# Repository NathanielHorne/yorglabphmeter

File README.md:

# yorglabphmeter
yorglabphmeter

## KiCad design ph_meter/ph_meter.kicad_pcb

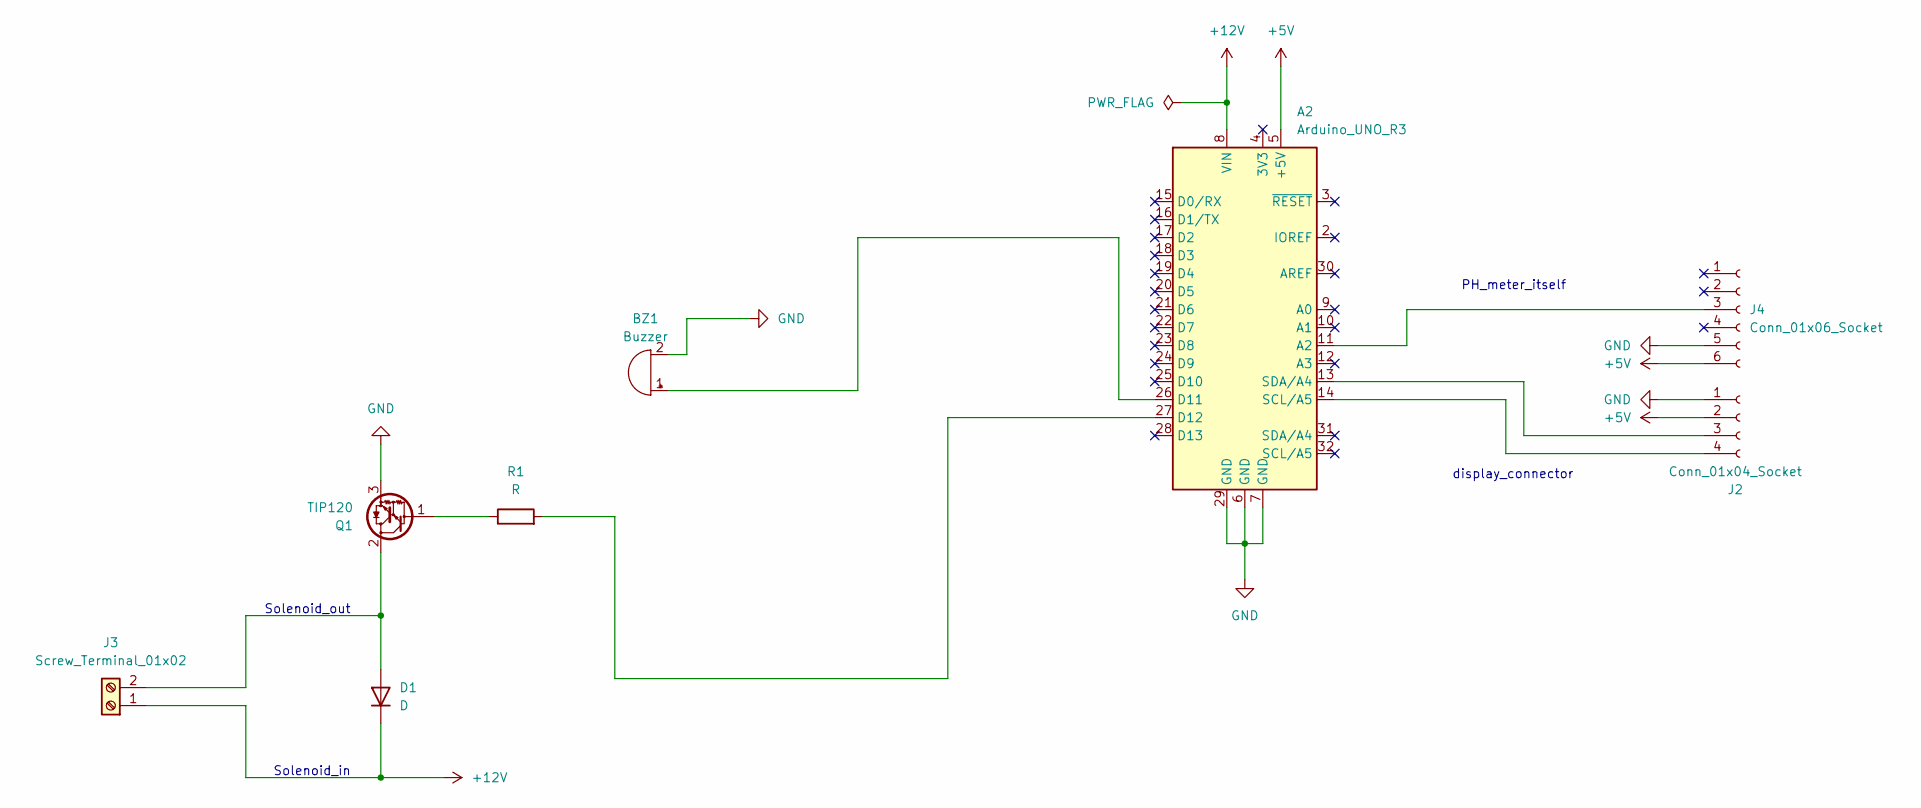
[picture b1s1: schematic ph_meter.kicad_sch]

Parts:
A2: Arduino_UNO_R3
BZ1: Buzzer; Buzzer_12x9.5RM7.6
D1: D; D_A-405_P10.16mm_Horizontal
J2: Conn_01x04_Socket; PinSocket_1x04_P2.54mm_Vertical
J3: Screw_Terminal_01x02; TerminalBlock_Altech_AK300-2_P5.00mm
J4: Conn_01x06_Socket; PinSocket_1x06_P2.54mm_Vertical
Q1: TIP120; TO-220-3_Vertical
R1: R; R_Axial_DIN0207_L6.3mm_D2.5mm_P10.16mm_Horizontal

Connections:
+5V: A2.5 (+5V), J2.2, J4.6
+12V: A2.8 (VIN), D1.1 (K), J3.1
GND: A2.6 (GND), A2.7 (GND), A2.29 (GND), BZ1.2 (+), J2.1, J4.5, Q1.3 (E)
unnamed: A2.11 (A2), J4.3
unnamed: A2.26 (D11), BZ1.1 (-)
unnamed: A2.27 (D12), R1.2
unnamed: D1.2 (A), J3.2, Q1.2 (C)
unnamed: A2.13 (SDA/A4), J2.3
unnamed: A2.14 (SCL/A5), J2.4
unnamed: Q1.1 (B), R1.1

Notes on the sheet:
display_connector
Solenoid_out
PH_meter_itself
Solenoid_in

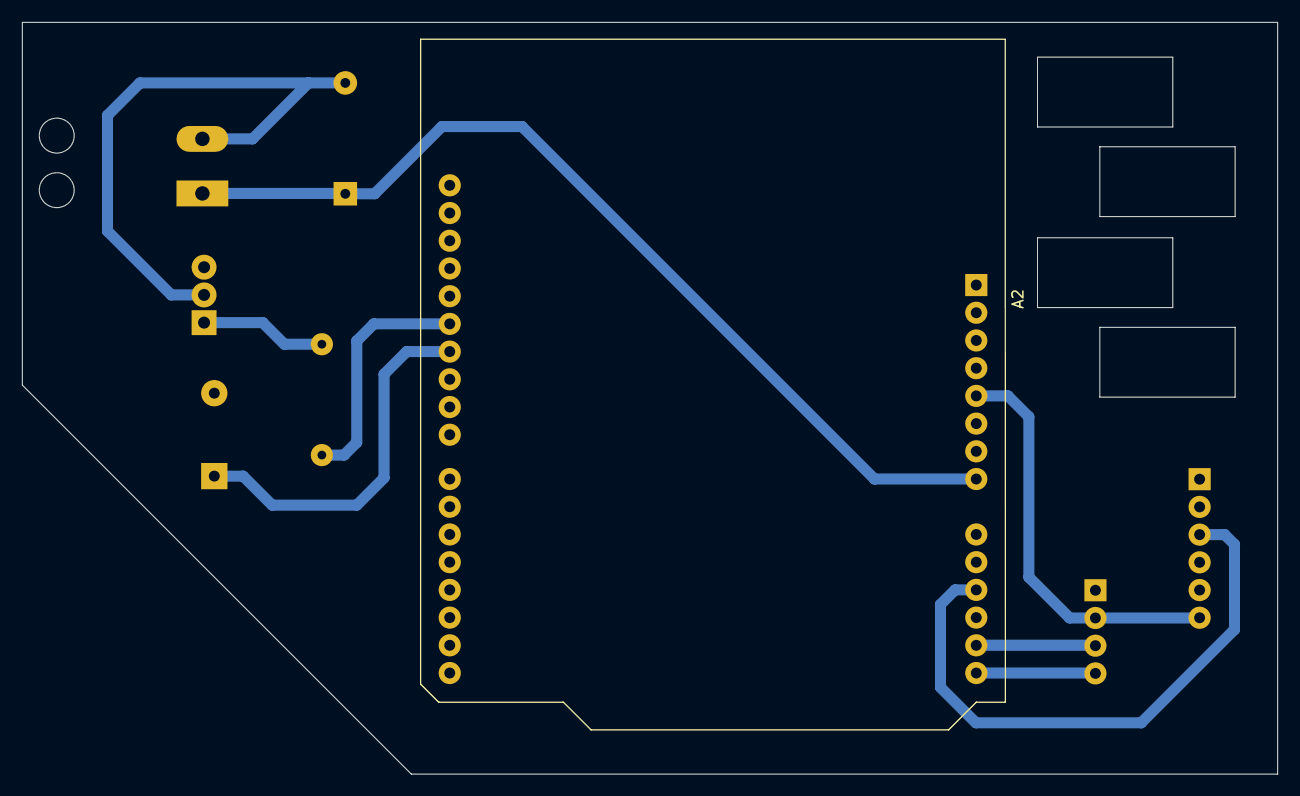
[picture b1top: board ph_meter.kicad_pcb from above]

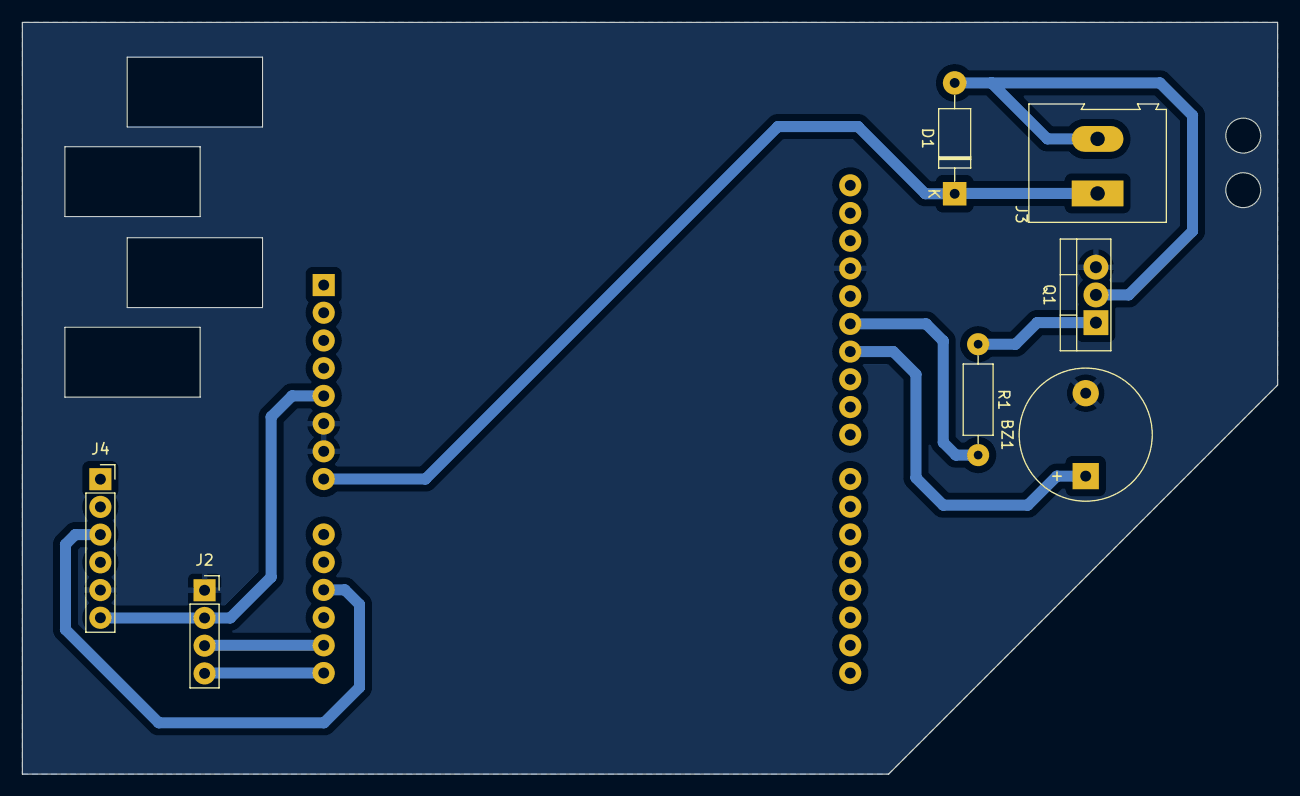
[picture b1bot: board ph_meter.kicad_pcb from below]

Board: 2 copper layers, 115.0 x 68.9 mm, 8 parts (7 on the bottom side), 10 nets.

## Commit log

2024-05-13 Upload previous files
